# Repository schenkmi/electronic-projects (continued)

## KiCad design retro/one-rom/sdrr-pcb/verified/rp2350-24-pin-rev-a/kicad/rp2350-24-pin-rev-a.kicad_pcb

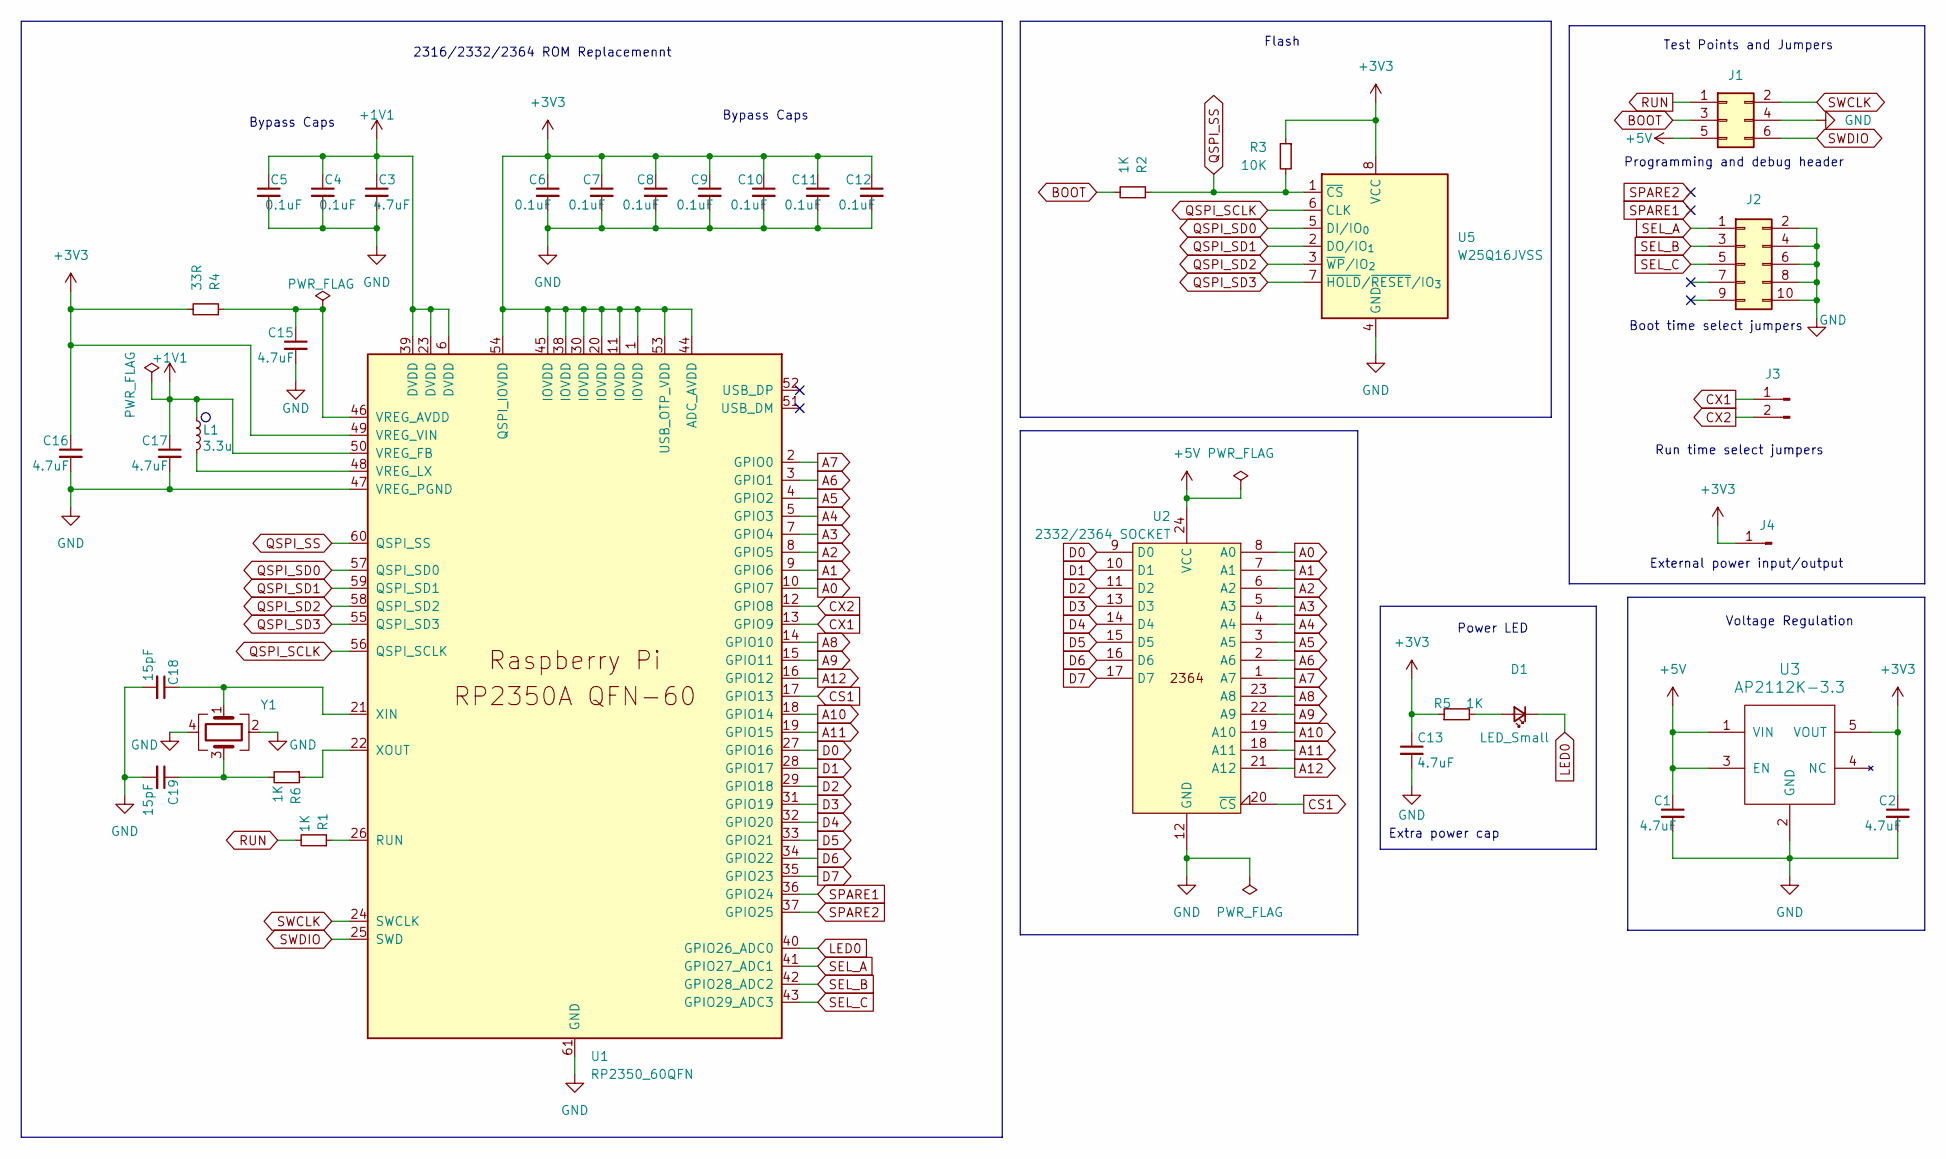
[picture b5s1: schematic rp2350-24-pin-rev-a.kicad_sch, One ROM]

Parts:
C1, C2, C3, C13, C15: 4.7uF; C_0402_1005Metric; LCSC C23733
C4, C5, C6, C7, C8, C9, C10, C11, C12: 0.1uF; C_0402_1005Metric; LCSC C1525
C16, C17: 4.7uF; C_0402_1005Metric_small_pads; LCSC C23733
C18, C19: 15pF; C_0402_1005Metric; LCSC C1548
D1: LED_Small; LED_0603_1608Metric; LCSC C2286
J1: Conn_02x03_Odd_Even; PinHeader_2x03_P2.54mm_Vertical
J2: Conn_02x05_Odd_Even; PinHeader_2x05_P2.54mm_Vertical custom silkscreen
J3: Conn_01x02_Pin; PinHeader_1x02_P2.54mm_Vertical
J4: Conn_01x01_Pin; PinHeader_1x01_P2.54mm_Vertical
L1: 3.3u; L_pol_2016; LCSC C42411119
R1, R2, R5, R6: 1K; R_0402_1005Metric; LCSC C11702
R3: 10K; R_0402_1005Metric; LCSC C25744
R4: 33R; R_0402_1005Metric; LCSC C25105
U1: RP2350_60QFN; RP2350-QFN-60-1EP_7x7_P0.4mm_EP3.4x3.4mm_ThermalVias; LCSC C42411118
U2: 2332/2364 SOCKET; 2x12 dip pin output 600mil centres no ss
U3: AP2112K-3.3; SOT-23-5; LCSC C51118
U5: W25Q16JVSS; Winbond_USON-8-1EP_3x2mm_P0.5mm_EP0.2x1.6mm; LCSC C2843335
Y1: Crystal_GND24; Crystal_SMD_Abracon_ABM8G-4Pin_3.2x2.5mm; LCSC C20625731

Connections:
+1V1: C3.1, C4.1, C5.1, C17.1, L1.1, U1.6 (DVDD), U1.23 (DVDD), U1.39 (DVDD), U1.50 (VREG_FB)
+3V3: C2.1, C6.1, C7.1, C8.1, C9.1, C10.1, C11.1, C12.1, C13.1, C16.1, J4.1, R3.1, R4.2, R5.1, U1.1 (IOVDD), U1.11 (IOVDD), U1.20 (IOVDD), U1.30 (IOVDD), U1.38 (IOVDD), U1.44 (ADC_AVDD), U1.45 (IOVDD), U1.49 (VREG_VIN), U1.53 (USB_OTP_VDD), U1.54 (QSPI_IOVDD), U3.5 (VOUT), U5.8 (VCC)
+5V: C1.1, J1.5, U2.24 (VCC), U3.1 (VIN), U3.3 (EN)
A0: U1.10 (GPIO7), U2.8 (A0)
A1: U1.9 (GPIO6), U2.7 (A1)
A2: U1.8 (GPIO5), U2.6 (A2)
A3: U1.7 (GPIO4), U2.5 (A3)
A4: U1.5 (GPIO3), U2.4 (A4)
A5: U1.4 (GPIO2), U2.3 (A5)
A6: U1.3 (GPIO1), U2.2 (A6)
A7: U1.2 (GPIO0), U2.1 (A7)
A8: U1.14 (GPIO10), U2.23 (A8)
A9: U1.15 (GPIO11), U2.22 (A9)
A10: U1.18 (GPIO14), U2.19 (A10)
A11: U1.19 (GPIO15), U2.18 (A11)
A12: U1.16 (GPIO12), U2.21 (A12)
BOOT: J1.3, R2.2
CS1: U1.17 (GPIO13), U2.20 (~CS)
CX1: J3.1, U1.13 (GPIO9)
CX2: J3.2, U1.12 (GPIO8)
D0: U1.27 (GPIO16), U2.9 (D0)
D1: U1.28 (GPIO17), U2.10 (D1)
D2: U1.29 (GPIO18), U2.11 (D2)
D3: U1.31 (GPIO19), U2.13 (D3)
D4: U1.32 (GPIO20), U2.14 (D4)
D5: U1.33 (GPIO21), U2.15 (D5)
D6: U1.34 (GPIO22), U2.16 (D6)
D7: U1.35 (GPIO23), U2.17 (D7)
GND: C1.2, C2.2, C3.2, C4.2, C5.2, C6.2, C7.2, C8.2, C9.2, C10.2, C11.2, C12.2, C13.2, C15.2, C16.2, C17.2, C18.2, C19.2, J1.4, J2.2, J2.4, J2.6, J2.8, J2.10, U1.47 (VREG_PGND), U1.61 (GND), U2.12 (GND), U3.2 (GND), U5.4 (GND), Y1.2, Y1.4
LED0: D1.1 (K), U1.40 (GPIO26_ADC0)
unnamed: C19.1, R6.2, Y1.3
unnamed: D1.2 (A), R5.2
unnamed: R1.1, U1.26 (RUN)
unnamed: C15.1, R4.1, U1.46 (VREG_AVDD)
unnamed: L1.2, U1.48 (VREG_LX)
unnamed: C18.1, U1.21 (XIN), Y1.1
unnamed: R6.1, U1.22 (XOUT)
QSPI_SCLK: U1.56 (QSPI_SCLK), U5.6 (CLK)
QSPI_SD0: U1.57 (QSPI_SD0), U5.5 (DI/IO_{0})
QSPI_SD1: U1.59 (QSPI_SD1), U5.2 (DO/IO_{1})
QSPI_SD2: U1.58 (QSPI_SD2), U5.3 (~WP/IO_{2})
QSPI_SD3: U1.55 (QSPI_SD3), U5.7 (~HOLD/~RESET/IO_{3})
QSPI_SS: R2.1, R3.2, U1.60 (QSPI_SS), U5.1 (~CS)
RUN: J1.1, R1.2
SEL_A: J2.1, U1.41 (GPIO27_ADC1)
SEL_B: J2.3, U1.42 (GPIO28_ADC2)
SEL_C: J2.5, U1.43 (GPIO29_ADC3)
SPARE1: U1.36 (GPIO24)
SPARE2: U1.37 (GPIO25)
SWCLK: J1.2, U1.24 (SWCLK)
SWDIO: J1.6, U1.25 (SWD)

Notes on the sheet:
Run time select jumpers
Voltage Regulation
Extra power cap
2316/2332/2364 ROM Replacemennt
Bypass Caps
Power LED
Programming and debug header
External power input/output
Flash
Boot time select jumpers
Test Points and Jumpers

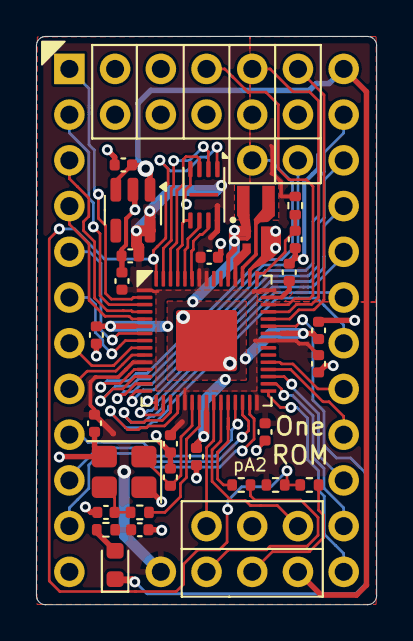
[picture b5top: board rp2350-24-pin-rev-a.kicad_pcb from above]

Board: 2 copper layers, 18.9 x 31.6 mm, 35 parts (0 on the bottom side), 49 nets.
